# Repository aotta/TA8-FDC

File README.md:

Forked and adapted from https://github.com/felge1966/Alphatronic-PC
Note: you have to solder the 50 pin bus connector on the solder side, since by mistake i mirrored odd & even pin in gerber

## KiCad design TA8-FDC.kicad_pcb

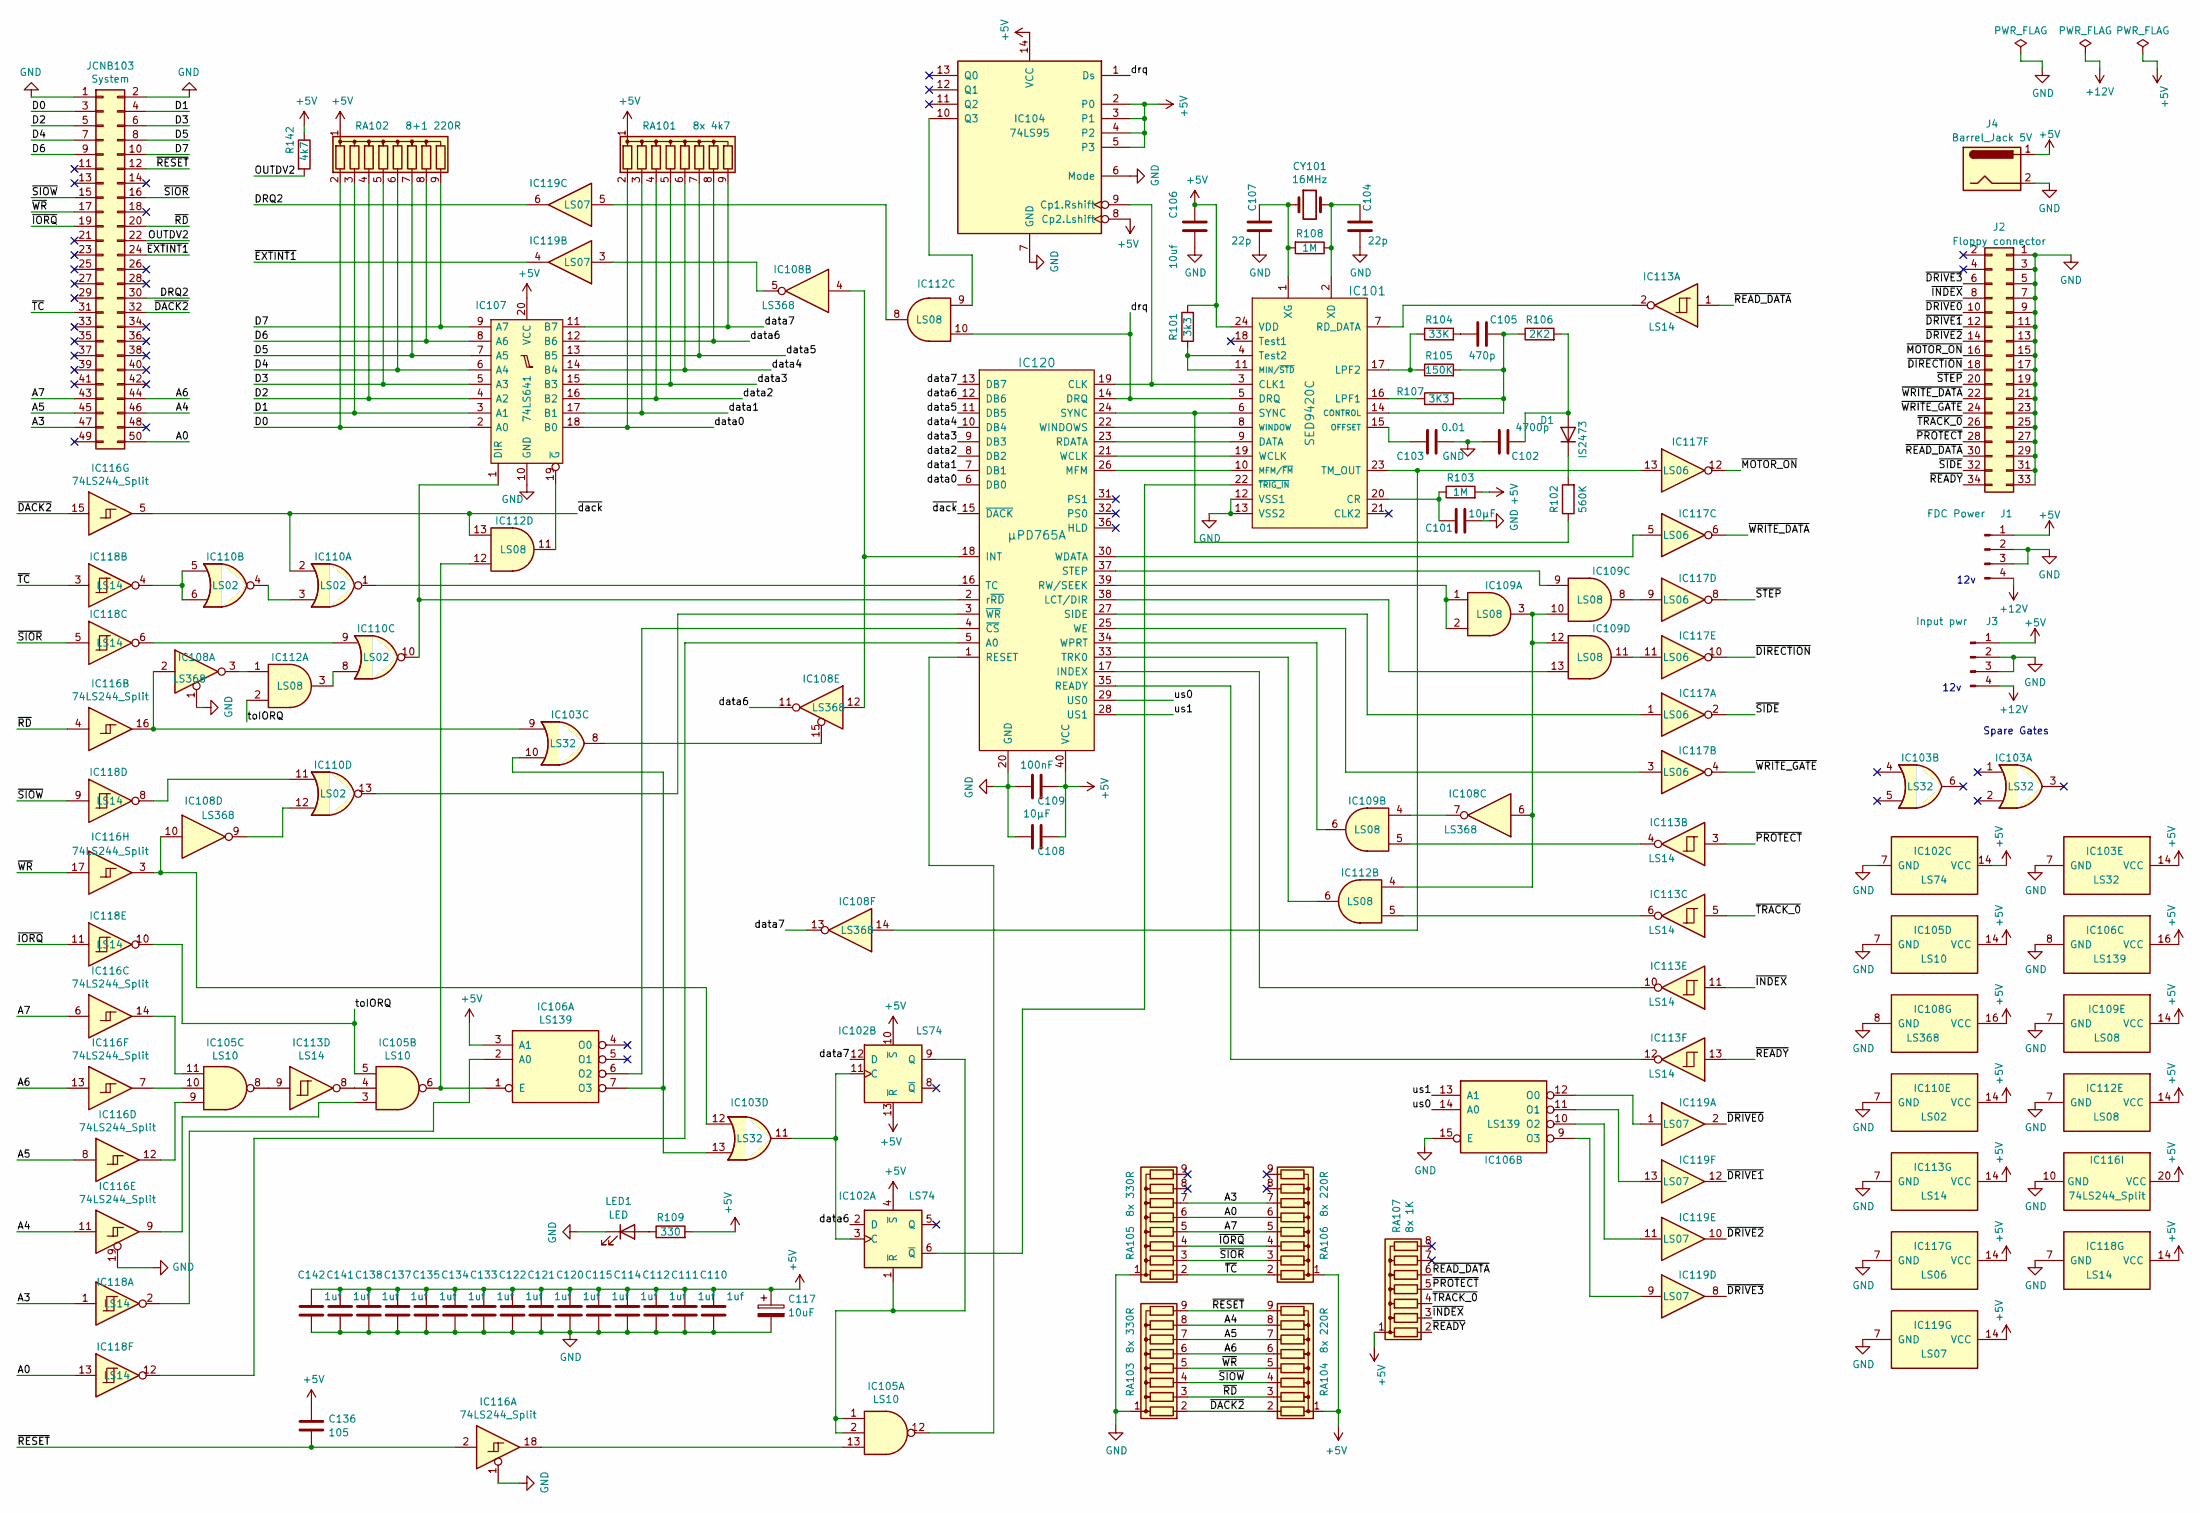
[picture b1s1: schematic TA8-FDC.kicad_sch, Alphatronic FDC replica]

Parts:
C101, C108: 10µF; CP_Axial_L10.0mm_D4.5mm_P15.00mm_Horizontal
C102: 4700p; C_Disc_D3.0mm_W2.0mm_P2.50mm
C103: 0.01; C_Disc_D3.0mm_W2.0mm_P2.50mm
C104, C107: 22p; C_Disc_D3.0mm_W2.0mm_P2.50mm
C105: 470p; C_Disc_D3.0mm_W2.0mm_P2.50mm
C106: 10uf; CP_Axial_L10.0mm_D4.5mm_P15.00mm_Horizontal
C109: 100nF; C_Disc_D3.0mm_W2.0mm_P2.50mm
C110, C111, C112, C114, C115, C120, C121, C122, C133, C134, C135, C137, C138, C141, C142: 1uf; C_Disc_D3.0mm_W2.0mm_P2.50mm
C117: 10uF; CP_Axial_L10.0mm_D4.5mm_P15.00mm_Horizontal
C136: 105; C_Axial_L3.8mm_D2.6mm_P7.50mm_Horizontal
CY101: 16MHz; Crystal_HC49-4H_Vertical
D1: IS2473; D_A-405_P10.16mm_Horizontal
IC101: SED9420C; DIP-24_W15.24mm
IC102: LS74; DIP-14_W7.62mm
IC103: LS32; DIP-14_W7.62mm
IC104: 74LS95; DIP-14_W7.62mm
IC105: LS10; DIP-14_W7.62mm
IC106: LS139; DIP-16_W7.62mm
IC107: 74LS641; DIP-20_W7.62mm
IC108: LS368; DIP-16_W7.62mm
IC109, IC112: LS08; DIP-14_W7.62mm
IC110: LS02; DIP-14_W7.62mm
IC113, IC118: LS14; DIP-14_W7.62mm
IC116: 74LS244_Split; DIP-20_W7.62mm
IC117: LS06; DIP-14_W7.62mm
IC119: LS07; DIP-14_W7.62mm
IC120: µPD765A; DIP-40_W15.24mm
J1: FDC Power; Molex_SL_171971-0004_1x04_P2.54mm_Vertical
J2: Floppy connector; IDC-Header_2x17_P2.54mm_Horizontal
J3: Input pwr; Molex_SL_171971-0004_1x04_P2.54mm_Vertical
J4: Barrel_Jack 5V; BarrelJack_Horizontal
JCNB103: System; PinSocket_2x25_P2.54mm_Horizontal
LED1: LED; LED_D3.0mm
R101: 3k3; R_Axial_DIN0207_L6.3mm_D2.5mm_P10.16mm_Horizontal
R102: 560K; R_Axial_DIN0207_L6.3mm_D2.5mm_P10.16mm_Horizontal
R103, R108: 1M; R_Axial_DIN0207_L6.3mm_D2.5mm_P10.16mm_Horizontal
R104: 33K; R_Axial_DIN0207_L6.3mm_D2.5mm_P10.16mm_Horizontal
R105: 150K; R_Axial_DIN0207_L6.3mm_D2.5mm_P10.16mm_Horizontal
R106: 2K2; R_Axial_DIN0207_L6.3mm_D2.5mm_P10.16mm_Horizontal
R107: 3K3; R_Axial_DIN0207_L6.3mm_D2.5mm_P10.16mm_Horizontal
R109: 330; R_Axial_DIN0207_L6.3mm_D2.5mm_P10.16mm_Horizontal
R142: 4k7; R_Axial_DIN0207_L6.3mm_D2.5mm_P10.16mm_Horizontal
RA101: 8x 4k7; R_Array_SIP9
RA102: 8+1 220R; R_Array_SIP9
RA103, RA105: 8x 330R; R_Array_SIP9
RA104, RA106: 8x 220R; R_Array_SIP9
RA107: 8x 1K; R_Array_SIP8

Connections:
+5V: C106.1, C108.1, C109.1, C110.2, C111.2, C112.2, C114.2, C115.2, C117.1, C120.2, C121.2, C122.2, C133.2, C134.2, C135.2, C136.2, C137.2, C138.2, C141.2, C142.2, IC101.24 (VDD), IC102.4 (~S), IC102.10 (~S), IC102.13 (~R), IC102.14 (VCC), IC103.14 (VCC), IC104.2 (P0), IC104.3 (P1), IC104.4 (P2), IC104.5 (P3), IC104.8 (Cp2.Lshift), IC104.14 (VCC), IC105.14 (VCC), IC106.3 (A1), IC106.16 (VCC), IC107.20 (VCC), IC108.16 (VCC), IC109.14 (VCC), IC110.14 (VCC), IC112.14 (VCC), IC113.14 (VCC), IC116.20 (VCC), IC117.14 (VCC), IC118.14 (VCC), IC119.14 (VCC), IC120.40 (VCC), J1.1, J3.1, J4.1, R101.2, R103.2, R109.2, R142.1, RA101.1 (common), RA102.1 (common), RA104.1 (common), RA106.1 (common), RA107.1 (common)
+12V: J1.4, J3.4
/A0: IC118.13, JCNB103.50, RA105.6 (R5), RA106.6 (R5)
/A3: IC118.1, JCNB103.47, RA105.7 (R6), RA106.7 (R6)
/A4: IC116.11, JCNB103.46, RA103.8 (R7), RA104.8 (R7)
/A5: IC116.8, JCNB103.45, RA103.7 (R6), RA104.7 (R6)
/A6: IC116.13, JCNB103.44, RA103.6 (R5), RA104.6 (R5)
/A7: IC116.6, JCNB103.43, RA105.5 (R4), RA106.5 (R4)
/D0: IC107.2 (A0), JCNB103.3, RA102.2 (R1)
/D1: IC107.3 (A1), JCNB103.4, RA102.3 (R2)
/D2: IC107.4 (A2), JCNB103.5, RA102.4 (R3)
/D3: IC107.5 (A3), JCNB103.6, RA102.5 (R4)
/D4: IC107.6 (A4), JCNB103.7, RA102.6 (R5)
/D5: IC107.7 (A5), JCNB103.8, RA102.7 (R6)
/D6: IC107.8 (A6), JCNB103.9, RA102.8 (R7)
/D7: IC107.9 (A7), JCNB103.10, RA102.9 (R8)
/DRQ2: IC119.6, JCNB103.30
/OUTDV2: JCNB103.22, R142.2
/data0: IC107.18 (B0), IC120.6 (DB0), RA101.2 (R1)
/data1: IC107.17 (B1), IC120.7 (DB1), RA101.3 (R2)
/data2: IC107.16 (B2), IC120.8 (DB2), RA101.4 (R3)
/data3: IC107.15 (B3), IC120.9 (DB3), RA101.5 (R4)
/data4: IC107.14 (B4), IC120.10 (DB4), RA101.6 (R5)
/data5: IC107.13 (B5), IC120.11 (DB5), RA101.7 (R6)
/data6: IC102.2 (D), IC107.12 (B6), IC108.11, IC120.12 (DB6), RA101.8 (R7)
/data7: IC102.12 (D), IC107.11 (B7), IC108.13, IC120.13 (DB7), RA101.9 (R8)
/drq: IC101.5 (DRQ), IC104.1 (Ds), IC112.10, IC120.14 (DRQ)
/toIORQ: IC105.5, IC112.2, IC118.10
/us0: IC106.14 (A0), IC120.29 (US0)
/us1: IC106.13 (A1), IC120.28 (US1)
/~DACK2: IC116.15, JCNB103.32, RA103.2 (R1), RA104.2 (R1)
/~DIRECTION: IC117.10, J2.18
/~DRIVE0: IC119.2, J2.10
/~DRIVE1: IC119.12, J2.12
/~DRIVE2: IC119.10, J2.14
/~DRIVE3: IC119.8, J2.6
/~EXTINT1: IC119.4, JCNB103.24
/~INDEX: IC113.11, J2.8, RA107.3 (R2)
/~IORQ: IC118.11, JCNB103.19, RA105.4 (R3), RA106.4 (R3)
/~MOTOR_ON: IC117.12, J2.16
/~PROTECT: IC113.3, J2.28, RA107.5 (R4)
/~RD: IC116.4, JCNB103.20, RA103.3 (R2), RA104.3 (R2)
/~READY: IC113.13, J2.34, RA107.2 (R1)
/~READ_DATA: IC113.1, J2.30, RA107.6 (R5)
/~RESET: C136.1, IC116.2, JCNB103.12, RA103.9 (R8), RA104.9 (R8)
/~SIDE: IC117.2, J2.32
/~SIOR: IC118.5, JCNB103.16, RA105.3 (R2), RA106.3 (R2)
/~SIOW: IC118.9, JCNB103.15, RA103.4 (R3), RA104.4 (R3)
/~STEP: IC117.8, J2.20
/~TC: IC118.3, JCNB103.31, RA105.2 (R1), RA106.2 (R1)
/~TRACK_0: IC113.5, J2.26, RA107.4 (R3)
/~WRITE_DATA: IC117.6, J2.22
/~WRITE_GATE: IC117.4, J2.24
/~WR: IC116.17, JCNB103.17, RA103.5 (R4), RA104.5 (R4)
/~dack: IC110.2, IC112.13, IC116.5, IC120.15 (~DACK)
GND: C101.2, C102.1, C103.2, C104.2, C106.2, C107.2, C108.2, C109.2, C110.1, C111.1, C112.1, C114.1, C115.1, C117.2, C120.1, C121.1, C122.1, C133.1, C134.1, C135.1, C137.1, C138.1, C141.1, C142.1, IC101.12 (VSS1), IC101.13 (VSS2), IC102.7 (GND), IC103.7 (GND), IC104.6 (Mode), IC104.7 (GND), IC105.7 (GND), IC106.8 (GND), IC106.15 (E), IC107.10 (GND), IC108.1, IC108.8 (GND), IC109.7 (GND), IC110.7 (GND), IC112.7 (GND), IC113.7 (GND), IC116.1, IC116.10 (GND), IC116.19, IC117.7 (GND), IC118.7 (GND), IC119.7 (GND), IC120.20 (GND), J1.2, J1.3, J2.1, J2.3, J2.5, J2.7, J2.9, J2.11, J2.13, J2.15, J2.17, J2.19, J2.21, J2.23, J2.25, J2.27, J2.29, J2.31, J2.33, J3.2, J3.3, J4.2, JCNB103.1, JCNB103.2, LED1.1 (K), RA103.1 (common), RA105.1 (common)
unnamed: C105.1, R104.2
unnamed: C102.2, D1.2 (A), R106.2
unnamed: D1.1 (K), R102.2
unnamed: IC101.3 (CLK1), IC104.9 (Cp1.Rshift), IC120.19 (CLK)
unnamed: C105.2, IC101.14 (CONTROL), R105.2, R106.1, R107.2
unnamed: C101.1, IC101.20 (CR), R103.1
unnamed: IC101.9 (DATA), IC120.23 (RDATA)
unnamed: IC101.16 (LPF1), R107.1
unnamed: IC101.17 (LPF2), R104.1, R105.1
unnamed: IC101.10 (MFM/~FM), IC120.26 (MFM)
unnamed: IC101.4 (Test2), IC101.11 (MIN/~STD), R101.1
unnamed: C103.1, IC101.15 (OFFSET)
unnamed: IC101.7 (RD_DATA), IC113.2
unnamed: IC101.6 (SYNC), IC120.24 (SYNC), R102.1
unnamed: IC101.23 (TM_OUT), IC108.14, IC117.13
unnamed: IC101.19 (WCLK), IC120.21 (WCLK)
unnamed: IC101.8 (WINDOW), IC120.22 (WINDOWS)
unnamed: C104.1, CY101.2, IC101.2 (XD), R108.1
unnamed: C107.1, CY101.1, IC101.1 (XG), R108.2
unnamed: IC101.22 (~TRIG_IN), IC102.6 (~Q)
unnamed: IC102.3 (C), IC102.11 (C), IC103.11
unnamed: IC102.1 (~R), IC102.9 (Q), IC105.1, IC105.2
unnamed: IC103.8, IC108.15
unnamed: IC103.9, IC108.2, IC116.16
unnamed: IC103.12, IC108.10, IC116.3
unnamed: IC104.10 (Q3), IC112.9
unnamed: IC105.3, IC116.9
unnamed: IC105.4, IC113.8
unnamed: IC105.8, IC113.9
unnamed: IC105.9, IC116.12
unnamed: IC105.10, IC116.7
unnamed: IC105.11, IC116.14
unnamed: IC105.13, IC116.18
unnamed: IC106.2 (A0), IC118.2
unnamed: IC105.6, IC106.1 (E), IC112.12
unnamed: IC106.6 (O2), IC120.4 (~CS)
unnamed: IC103.10, IC103.13, IC106.7 (O3)
unnamed: IC106.12 (O0), IC119.1
unnamed: IC106.11 (O1), IC119.13
unnamed: IC106.10 (O2), IC119.11
unnamed: IC106.9 (O3), IC119.9
unnamed: IC107.1 (DIR), IC110.10, IC120.2 (r~RD)
unnamed: IC107.19 (~G), IC112.11
unnamed: IC108.3, IC112.1
unnamed: IC108.5, IC119.3
unnamed: IC108.6, IC109.3, IC109.10, IC109.12, IC112.4
unnamed: IC108.7, IC109.4
unnamed: IC108.9, IC110.12
unnamed: IC109.5, IC113.4
unnamed: IC109.8, IC117.9
unnamed: IC109.11, IC117.11
unnamed: IC110.3, IC110.4
unnamed: IC110.5, IC110.6, IC118.4
unnamed: IC110.8, IC112.3
unnamed: IC110.9, IC118.6
unnamed: IC110.11, IC118.8
unnamed: IC112.5, IC113.6
unnamed: IC112.8, IC119.5
unnamed: IC118.12, IC120.5 (A0)
unnamed: IC113.10, IC120.17 (INDEX)
unnamed: IC108.4, IC108.12, IC120.18 (INT)
unnamed: IC109.13, IC120.38 (LCT/DIR)
unnamed: IC113.12, IC120.35 (READY)
unnamed: IC105.12, IC120.1 (RESET)
unnamed: IC109.1, IC109.2, IC120.39 (RW/SEEK)
unnamed: IC117.1, IC120.27 (SIDE)
unnamed: IC109.9, IC120.37 (STEP)
unnamed: IC110.1, IC120.16 (TC)
unnamed: IC112.6, IC120.33 (TRK0)
unnamed: IC117.5, IC120.30 (WDATA)
unnamed: IC117.3, IC120.25 (WE)
unnamed: IC109.6, IC120.34 (WPRT)
unnamed: IC110.13, IC120.3 (~WR)
unnamed: LED1.2 (A), R109.1

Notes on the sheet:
Spare Gates
12v

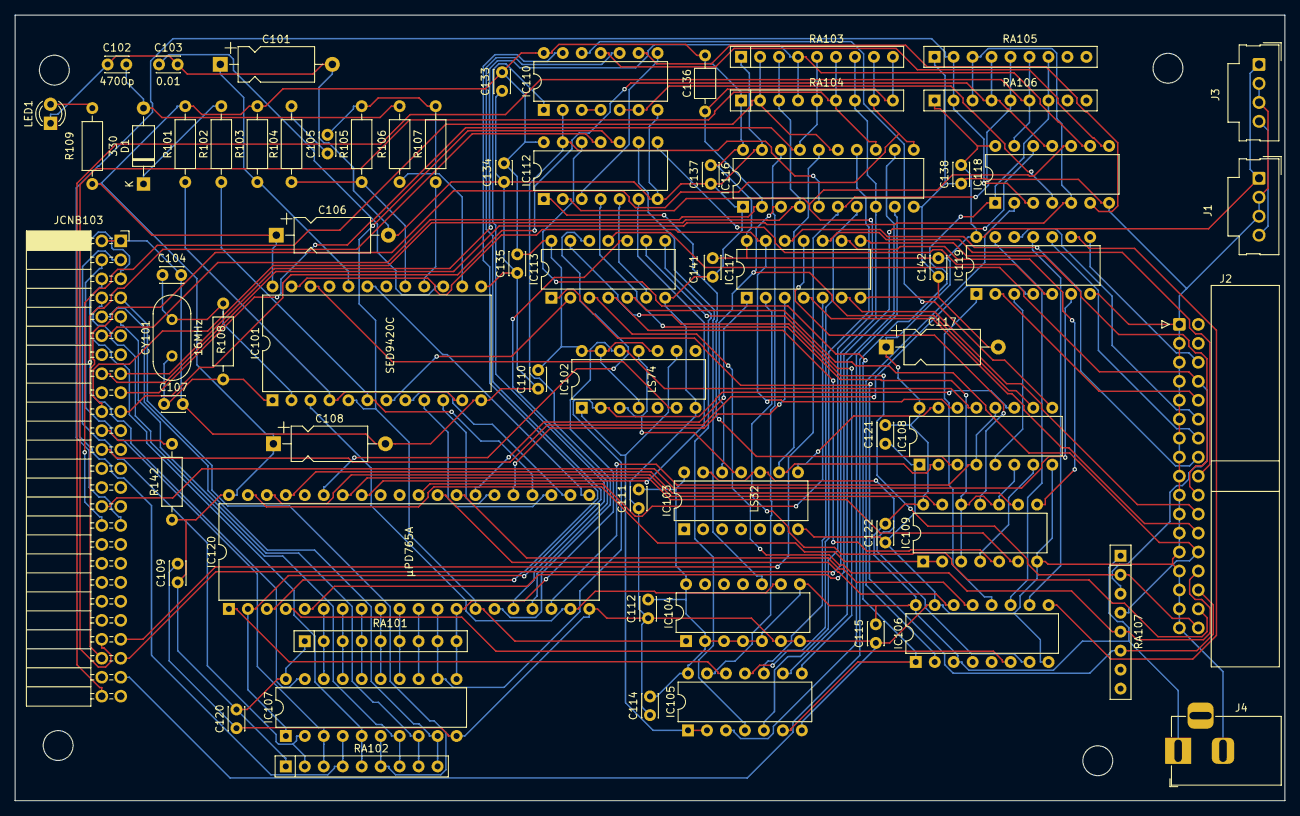
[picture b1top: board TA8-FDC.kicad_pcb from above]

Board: 2 copper layers, 170.0 x 105.2 mm, 68 parts (0 on the bottom side), 130 nets.

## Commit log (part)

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2023-12-30 Add files via upload
    initial load
2024-01-02 Add files via upload
    corrected a couple of error on schematics
2024-02-07 Add files via upload
    updated and working version
2024-02-15 Fixed C117
